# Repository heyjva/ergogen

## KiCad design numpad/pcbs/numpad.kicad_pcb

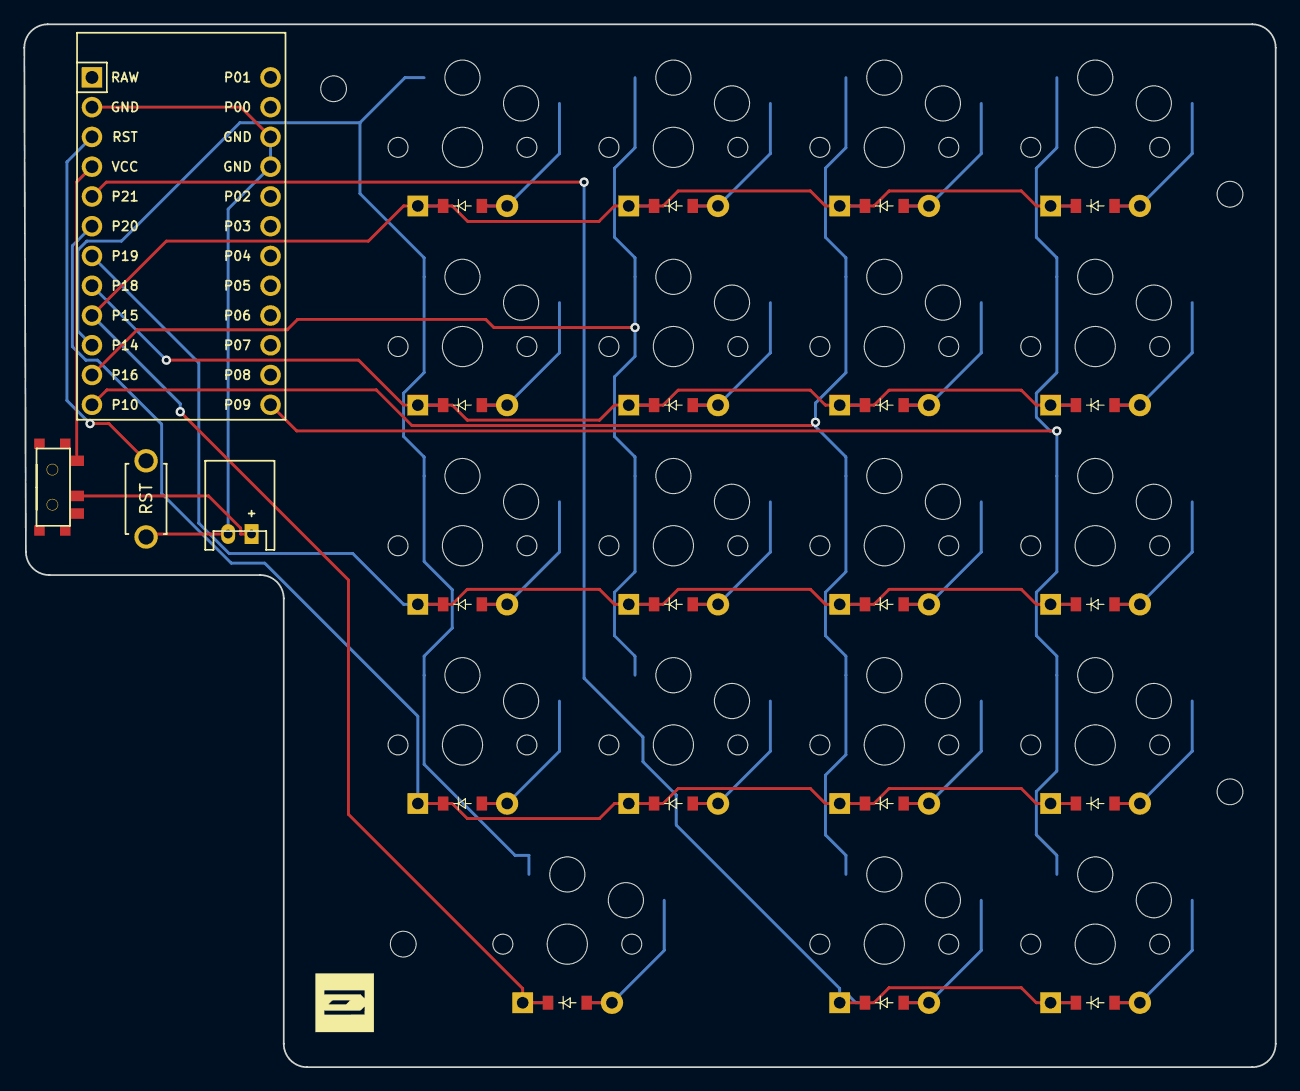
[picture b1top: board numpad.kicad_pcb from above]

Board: 2 copper layers, 106.8 x 89.0 mm, 47 parts (0 on the bottom side), 32 nets.

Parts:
D1, D2, D3, D4, D5, D6, D7, D8, D9, D10, D11, D12, D13, D14, D15, D16, D17, D18, D19: ComboDiode
JST1: JST_PH_S2B-PH-K_02x2.00mm_Angled
LOGO1: utility_ergogen_logo
MCU1: ProMicro
MH1, MH2, MH3, MH4: mounting_hole_npth
RST1: reset_switch_tht_top
S1, S2, S3, S4, S5, S6, S7, S8, S9, S10, S11, S12, S13, S14, S15, S16, S17, S18, S19: PG1350
T1: SPDT_C128955

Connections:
GND: JST1.2, MCU1.2, MCU1.15, MCU1.16, RST1.2
P01: JST1.1, T1.2
P9: MCU1.24, S14.1, S15.1, S16.1, S17.1, S18.1
P10: MCU1.12, S9.1, S10.1, S11.1, S12.1, S13.1
P14: MCU1.10, S1.1, S2.1, S3.1, S4.1, S19.1
P15: D4.1, D8.1, D13.1, D18.1, D19.1, MCU1.9
P16: MCU1.11, S5.1, S6.1, S7.1, S8.1
P18: D3.1, D7.1, D12.1, D17.1, MCU1.8
P19: D2.1, D6.1, D11.1, D16.1, MCU1.7
P20: D1.1, D5.1, D10.1, D15.1, MCU1.6
P21: D9.1, D14.1, MCU1.5
RST: MCU1.3, RST1.1
VCC: MCU1.4, T1.1
four_bottom: D15.2, S15.2
four_floor: D14.2, S14.2
four_home: D16.2, S16.2
four_num: D18.2, S18.2
four_top: D17.2, S17.2
one_bottom: D1.2, S1.2
one_home: D2.2, S2.2
one_num: D4.2, S4.2
one_top: D3.2, S3.2
three_bottom: D10.2, S10.2
three_floor: D9.2, S9.2
three_home: D11.2, S11.2
three_num: D13.2, S13.2
three_top: D12.2, S12.2
two_bottom: D5.2, S5.2
two_home: D6.2, S6.2
two_num: D8.2, S8.2
two_top: D7.2, S7.2
zero_only: D19.2, S19.2

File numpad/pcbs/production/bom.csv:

Designator,Footprint,Quantity,Value,LCSC Part #
"D1, D10, D11, D12, D13, D14, D15, D16, D17, D18, D19, D2, D3, D4, D5, D6, D7, D8, D9",ComboDiode,19,,
JST1,JST_PH_S2B-PH-K_02x2.00mm_Angled,1,,
MCU1,ProMicro,1,,
"MH1, MH2, MH3, MH4",mounting_hole_npth,4,,
RST1,reset_switch_tht_top,1,,
"S1, S10, S11, S12, S13, S14, S15, S16, S17, S18, S19, S2, S3, S4, S5, S6, S7, S8, S9",PG1350,19,,
T1,SPDT_C128955,1,,

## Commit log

2023-12-19 first update. keyboard and a lot of footprints
2023-12-22 latest stuff
2024-01-15 Refactor code for improved performance
2024-07-04 mainnumpad
2024-07-19 error label
2024-08-19 new json
